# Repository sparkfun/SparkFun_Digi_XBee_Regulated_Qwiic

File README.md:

SparkFun Digi XBee® Explorer Regulated
========================================

[*SparkFun Digi XBee® Explorer Regulated (22032)*](https://www.sparkfun.com/products/22032)

Unleash the power of Digi XBee® modules with the next-gen SparkFun Digi XBee® Explorer Regulated! This versatile breakout board bypasses a USB-C connection, packing all the XBee functionality you need alongside the power of Digi's newest XBee 3 modules (XBee 3 LTE-M/NB-IoT and XBee RR Pro) into a single, convenient solution. The SparkFun Digi XBee® Explorer Regulated is the perfect companion for any low-power cellular IoT project. Its simplicity, versatility, and robust features make it ideal for beginners and seasoned developers.

The SparkFun Digi XBee® Explorer Regulated streamlines your workflow, providing everything you need to get started. Power is provided through the PTH headers, and the board retains its power regulation capabilities. You can enable the Qwiic connector for all those lovely I<sup>2</sup>C sensors and Reset and D0 buttons.

Repository Contents
-------------------

* **/Hardware** - Eagle design files (.brd, .sch)
* **/Production** - Production panel files (.brd)
* **/docs** - Related software for the Sparkfun Digi XBee® Arduino Shield

Documentation
--------------
* **[Hookup Guide](http://docs.sparkfun.com/SparkFun_Digi_XBee_Regulated_Qwiic)** - Basic hookup guide for the SparkFun Digi XBee® Explorer Regulated.

License Information
-------------------

This product is _**open source**_! 

Please review the LICENSE.md file for license information. 

If you have any questions or concerns on licensing, please contact technical support on our [SparkFun forums](https://forum.sparkfun.com/viewforum.php?f=152).

Distributed as-is; no warranty is given.

- Your friends at SparkFun.

_<COLLABORATION CREDIT>_

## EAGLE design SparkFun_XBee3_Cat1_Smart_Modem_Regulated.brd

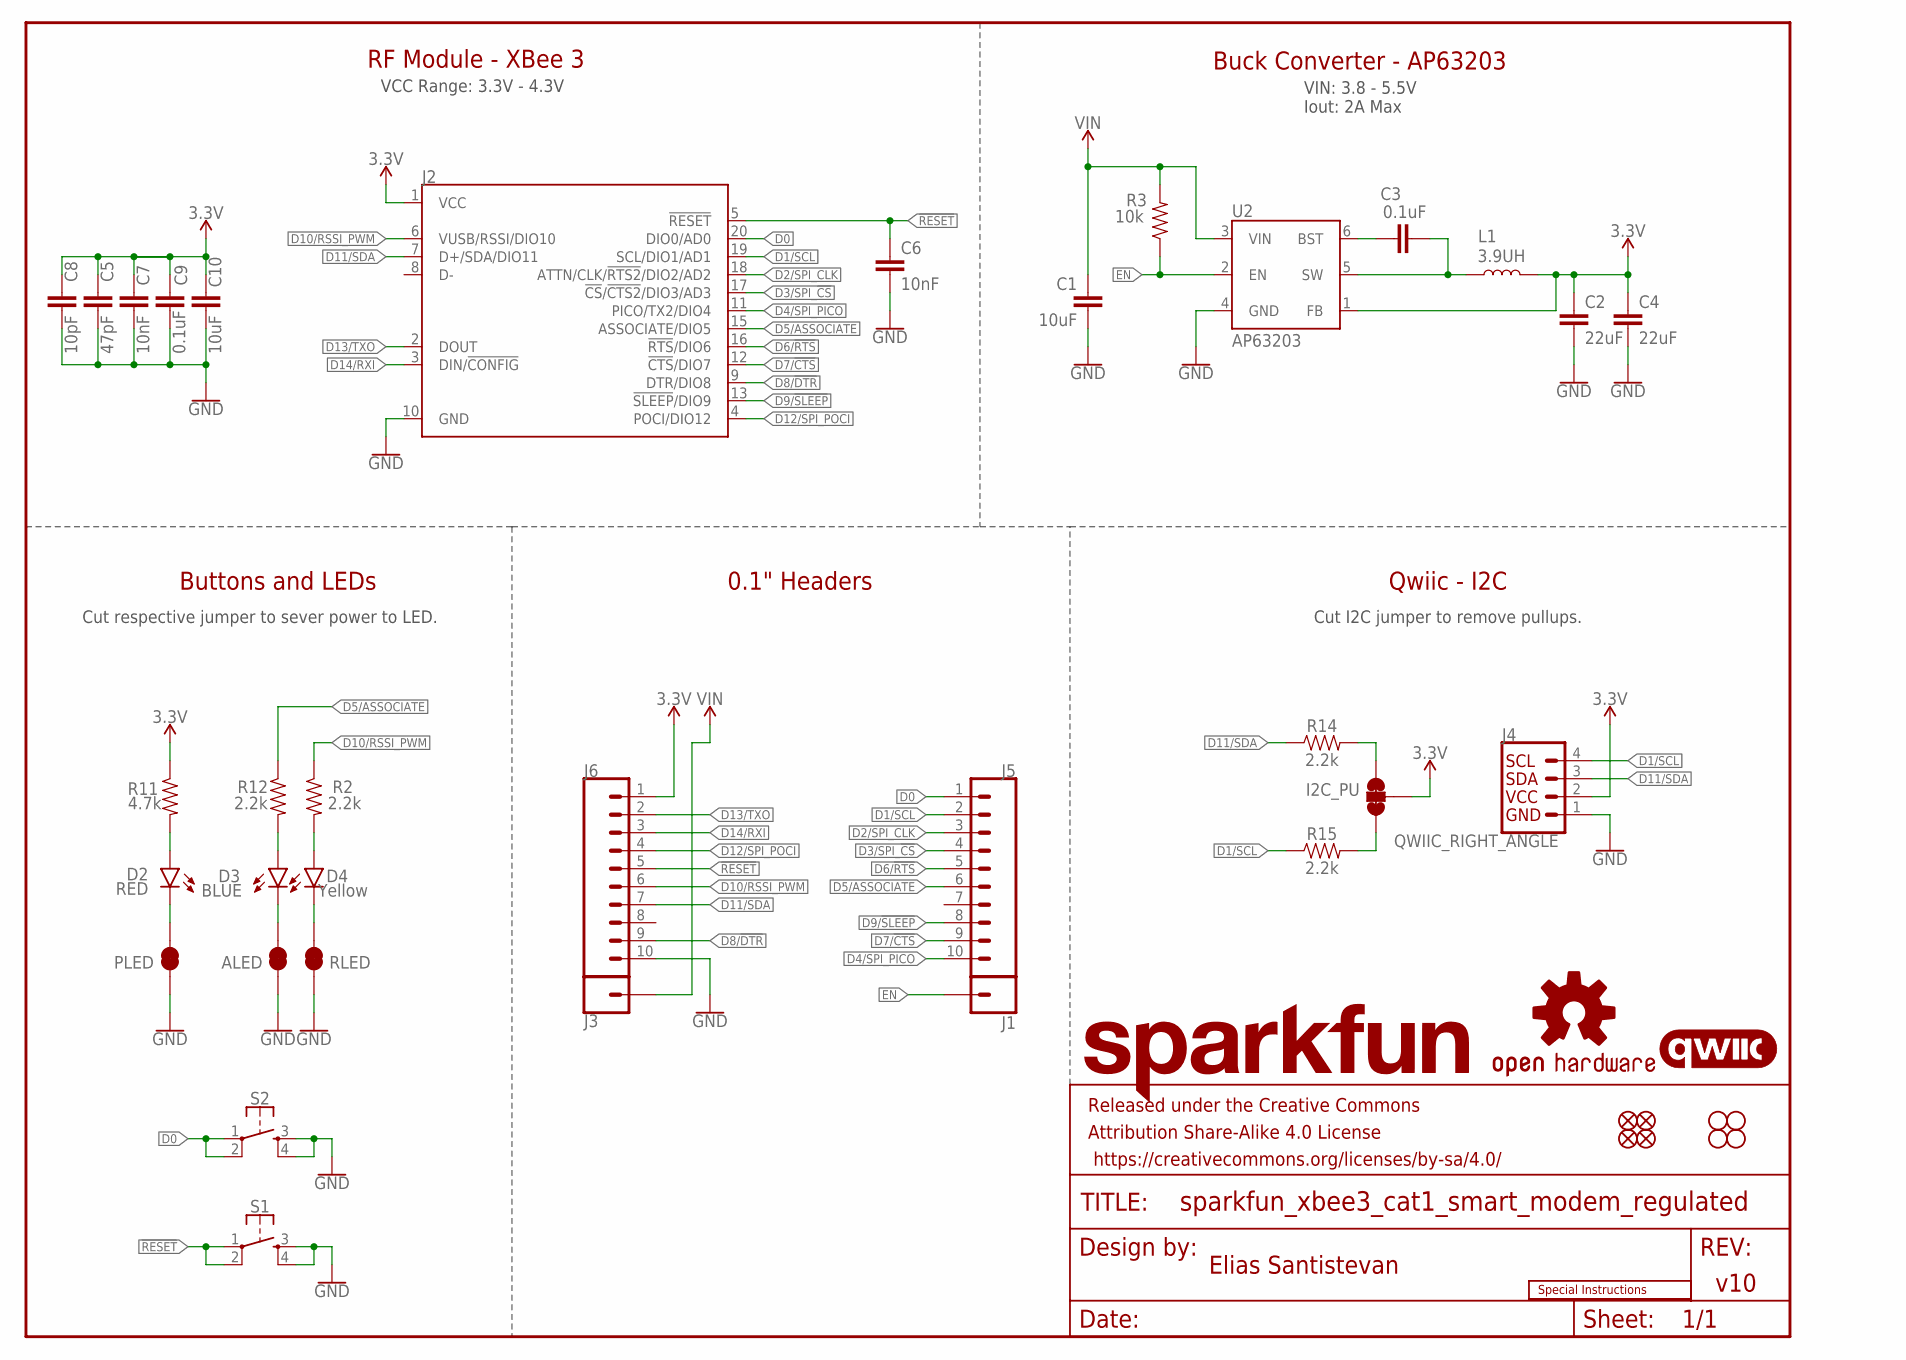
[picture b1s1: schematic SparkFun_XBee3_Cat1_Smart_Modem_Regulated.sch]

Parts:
ALED: JUMPER-SMT_2_NC_TRACE_SILK; SMT-JUMPER_2_NC_TRACE_SILK
C1: 10uF; 1210
C2, C4: 22uF; 0603
C3, C9: 0.1uF; 0603
C5: 47pF; 0603
C6, C7: 10nF; 0603
C8: 10pF; 0603
C10: 10uF; 0603
D2: RED; LED-0603
D3: BLUE; LED-0603
D4: Yellow; LED-0603
FD1, FD2, FD3, FD4: FIDUCIAL1X2; FIDUCIAL-1X2
FRAME2: FRAME-LETTER; CREATIVE_COMMONS
H1, H2, H3, H4: STAND-OFFTIGHT; STAND-OFF-TIGHT
I2C_PU: JUMPER-SMT_3_2-NC_TRACE_SILK; SMT-JUMPER_3_2-NC_TRACE_SILK
J1, J3: CONN_01PTH_NO_SILK_STAND; 1X01_NO_SILK_STAND
J2: XBEE_UPDATEXBEE_SMD; XBEE3-SMD
J4: QWIIC_RIGHT_ANGLE; JST04_1MM_RA
J5, J6: CONN_10NO_SILK_PTH_FEMALE; 1X10_NO_SILK
L1: 3.9UH; INDUCTOR_3.9UH
LOGO1: SPECIAL_INSTRUCTIONS-ORDERING; ORDERING_INSTRUCTIONS
LOGO2: OSHW-LOGOS; OSHW-LOGO-S
LOGO3: QWIIC_LOGO_4MM; QWIIC_4MM
LOGO4: SFE_LOGO_NAMEBLANK; BLANK
PLED: JUMPER-SMT_2_NC_TRACE_SILK; SMT-JUMPER_2_NC_TRACE_SILK
R2, R12, R14, R15: 2.2k; 0603
R3: 10k; 0603
R11: 4.7k; 0603
RLED: JUMPER-SMT_2_NC_TRACE_SILK; SMT-JUMPER_2_NC_TRACE_SILK
S1, S2: MOMENTARY-SWITCH-SPST-2-SMD-5.2MM-TALL; TACTILE_SWITCH_SMD_5.2MM
U2: AP63203; SOT23-6

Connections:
3.3V: C2.1, C4.1, C5.1, C7.1, C8.1, C9.1, C10.1, I2C_PU.2, J2.1 (VCC), J4.2, J6.1, L1.P$2 (2), R11.1, U2.1 (FB)
!RESET!: C6.1, J2.5 (!RESET!), J6.5, S1.1, S1.2
D0: J2.20 (DIO0/AD0), J5.1, S2.1, S2.2
D1/SCL: J2.19 (SCL/DIO1/AD1), J4.4, J5.2, R15.1
D2/SPI_CLK: J2.18 (ATTN/CLK/!RTS2!/DIO2/AD2), J5.3
D3/SPI_!CS!: J2.17 (!CS!/!CTS2!/DIO3/AD3), J5.4
D4/SPI_PICO: J2.11 (PICO/TX2/DIO4), J5.10
D5/ASSOCIATE: J2.15 (ASSOCIATE/DIO5), J5.6, R12.1
D6/!RTS!: J2.16 (!RTS!/DIO6), J5.5
D7/!CTS!: J2.12 (!CTS!/DIO7), J5.9
D8/!DTR!: J2.9 (DTR/DIO8), J6.9
D9/!SLEEP!: J2.13 (!SLEEP!/DIO9), J5.8
D10/RSSI_PWM: J2.6 (VUSB/RSSI/DIO10), J6.6, R2.1
D11/SDA: J2.7 (D+/SDA/DIO11), J4.3, J6.7, R14.1
D12/SPI_POCI: J2.4 (POCI/DIO12), J6.4
D13/TXO: J2.2 (DOUT), J6.2
D14/RXI: J2.3 (DIN/!CONFIG!), J6.3
EN: J1.1, R3.1, U2.2 (EN)
GND: ALED.1, C1.2, C2.2, C4.2, C5.2, C6.2, C7.2, C8.2, C9.2, C10.2, J2.10 (GND), J4.1, J6.10, PLED.1, RLED.1, S1.3, S1.4, S2.3, S2.4, U2.4 (GND)
unnamed: C3.1, U2.6 (BST)
unnamed: D4.A, R2.2
unnamed: D4.C, RLED.2
unnamed: D2.A, R11.2
unnamed: C3.2, L1.P$1 (1), U2.5 (SW)
unnamed: I2C_PU.3, R14.2
unnamed: D3.A, R12.2
unnamed: I2C_PU.1, R15.2
unnamed: ALED.2, D3.C
unnamed: D2.C, PLED.2
VIN: C1.1, J3.1, R3.2, U2.3 (VIN)

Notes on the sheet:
VCC Range: 3.3V - 4.3V
Buck Converter - AP63203
Qwiic - I2C
v10
Elias Santistevan
Buttons and LEDs
VIN: 3.8 - 5.5V Iout: 2A Max
Cut I2C jumper to remove pullups.
Cut respective jumper to sever power to LED.
RF Module - XBee 3
0.1" Headers

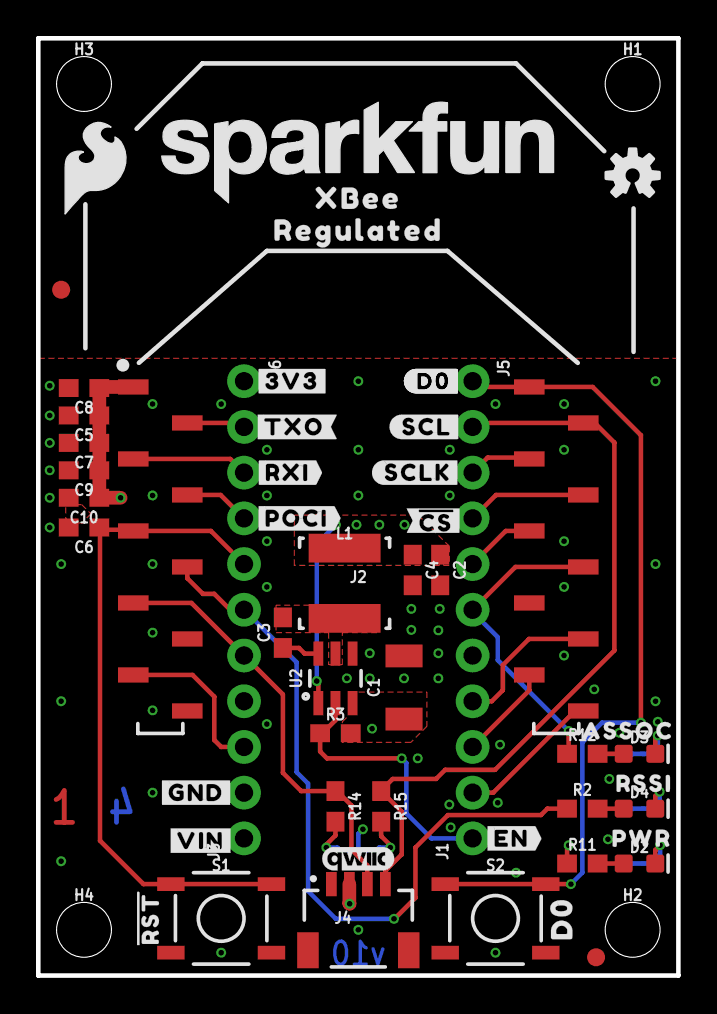
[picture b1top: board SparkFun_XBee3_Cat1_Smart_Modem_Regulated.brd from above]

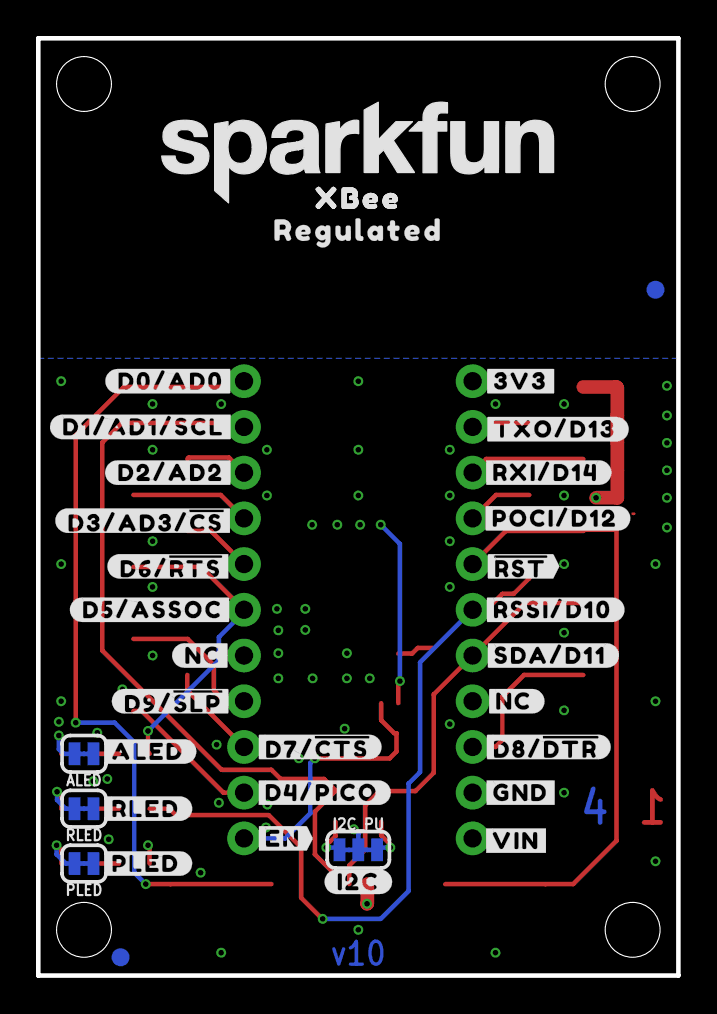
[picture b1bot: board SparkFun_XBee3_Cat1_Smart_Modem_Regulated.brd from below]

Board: 4 copper layers, 35.6 x 52.1 mm, 97 parts (36 on the bottom side), 30 nets.

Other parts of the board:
U$1, U$12: #GND#0
U$2, U$63: SFE_LOGO_NAME_.2
U$3, U$6: #EN#17
U$4: #NC#1
U$5: #NC#3
U$7: #D7##CTS##26
U$8: #D0#AD0#18
U$9, U$44: #3V3#1
U$10: #D4#PICO#25
U$11: #RLED#22
U$13: #D8##DTR##27
U$14: #RSSI#D10#17
U$15: #SDA#D11#9
U$16: ##RST##15
U$17: #POCI#D12#24
U$18: #RXI#D14#15
U$19: #D2#AD2#19
U$20: #D6##RTS##25
U$21: #TXO#8
U$22: #TXO#D13#13
U$23, U$25, U$28: XBEE340
U$24, U$29: REGULATED1343
U$26: #I2C#33
U$27: #RXI#7
U$30: #RST#30
U$31, U$65: #D0#3
U$32: #D1#AD1#SCL#8
U$34: #D3#AD3##CS##23
U$35: #D5#ASSOC#25
U$36: #D9##SLP##28
U$40: D03
U$42: PWR26
U$43: ASSOC27
U$45: #POCI#32
U$46, U$66: #VIN#4
U$49: #ALED#21
U$52: #PLED#20
U$59: ##CS##26
U$60: #SCLK#33
U$61: SFE_LOGO_FLAME_.2
U$62: RSSI31
U$64: #SCL#9

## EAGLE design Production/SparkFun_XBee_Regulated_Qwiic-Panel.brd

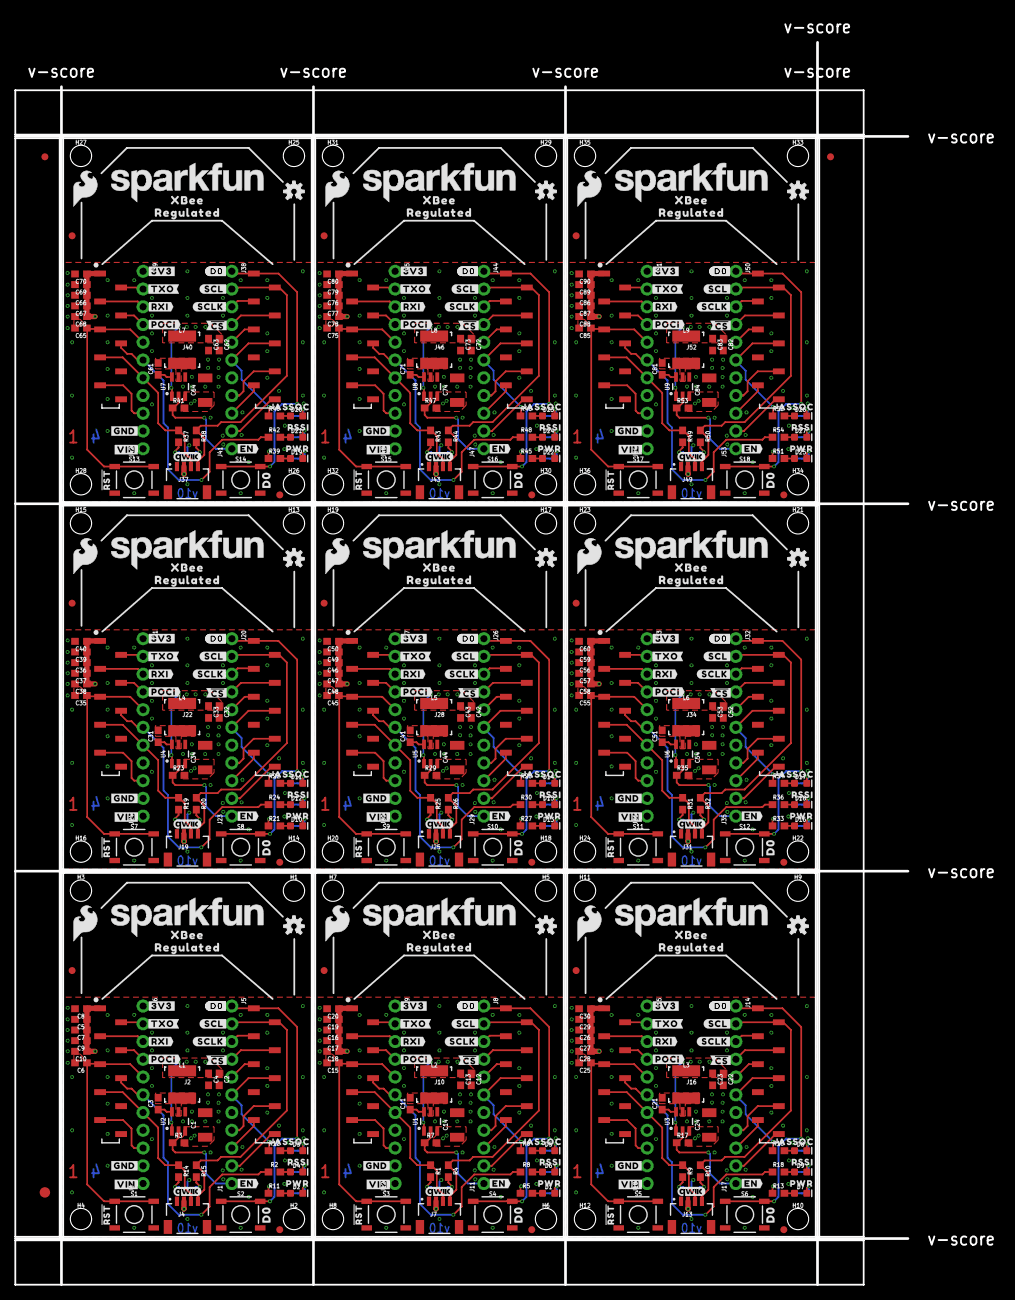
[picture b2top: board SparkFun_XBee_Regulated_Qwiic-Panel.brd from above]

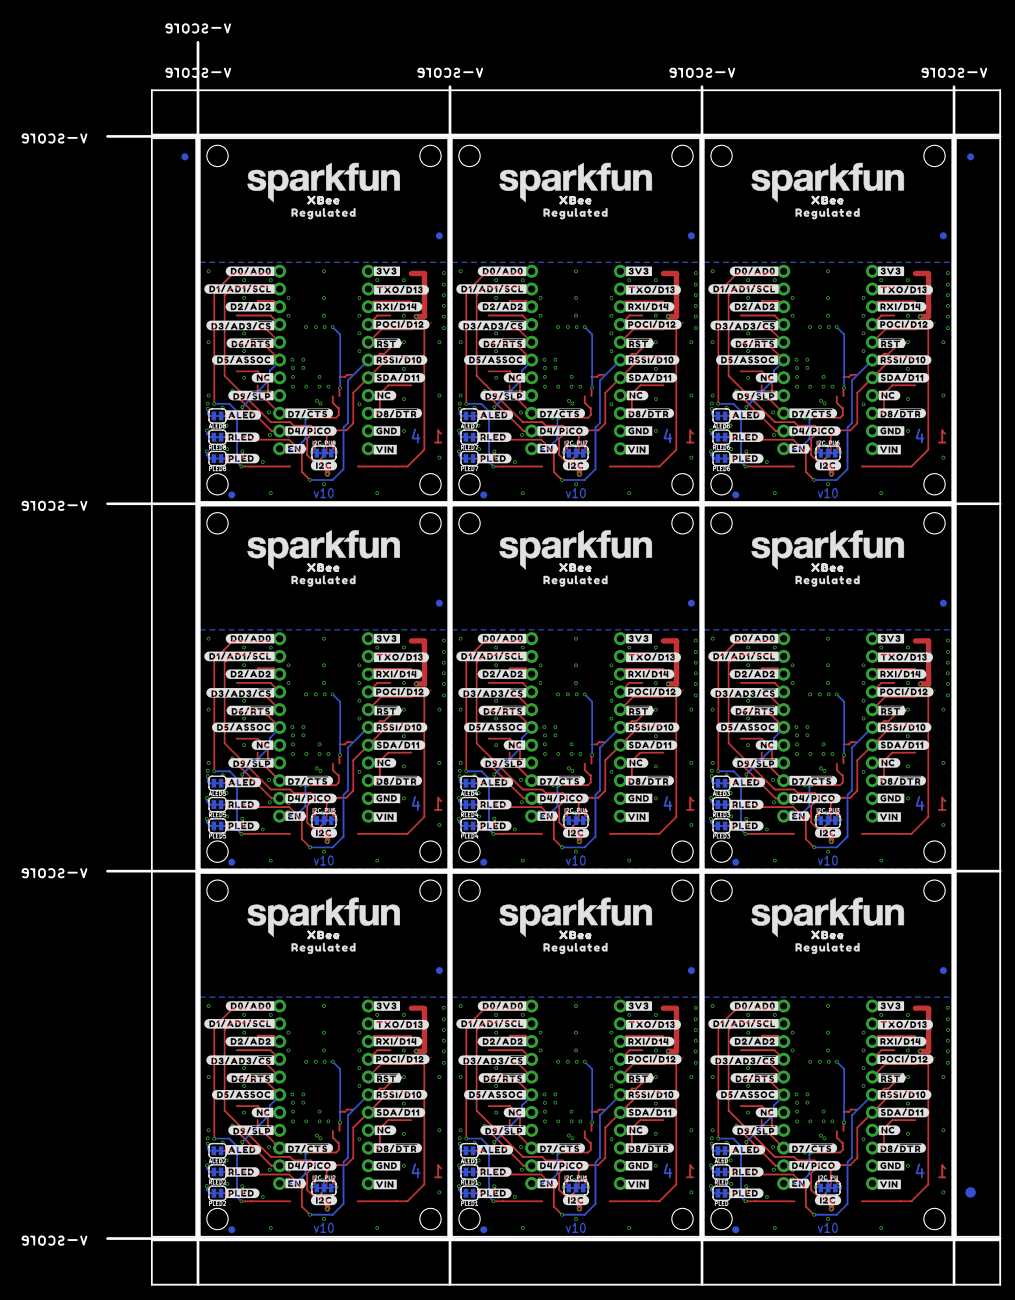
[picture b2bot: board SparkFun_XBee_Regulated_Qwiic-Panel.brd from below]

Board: 4 copper layers, 127.8 x 177.8 mm, 870 parts (327 on the bottom side), 270 nets.

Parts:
ALED, ALED1, ALED2, ALED3, ALED4, ALED5, ALED6, ALED7, ALED8: JUMPER-SMT_2_NC_TRACE_SILK; SMT-JUMPER_2_NC_TRACE_SILK
C1, C14, C24, C34, C44, C54, C64, C74, C84: 10uF; 1210
C2, C4, C12, C13, C22, C23, C32, C33, C42, C43, C52, C53, C62, C63, C72, C73, C82, C83: 22uF; 0603
C3, C9, C11, C17, C21, C27, C31, C37, C41, C47, C51, C57, C61, C67, C71, C77, C81, C87: 0.1uF; 0603
C5, C19, C29, C39, C49, C59, C69, C79, C89: 47pF; 0603
C6, C7, C15, C16, C25, C26, C35, C36, C45, C46, C55, C56, C65, C66, C75, C76, C85, C86: 10nF; 0603
C8, C20, C30, C40, C50, C60, C70, C80, C90: 10pF; 0603
C10, C18, C28, C38, C48, C58, C68, C78, C88: 10uF; 0603
D1, D2, D7, D10, D13, D16, D19, D22, D25: RED; LED-0603
D3, D5, D8, D11, D14, D17, D20, D23, D26: BLUE; LED-0603
D4, D6, D9, D12, D15, D18, D21, D24, D27: Yellow; LED-0603
E$1, E$2, E$3, E$4: FIDUCIAL-1X2
E$5, E$6: FIDUCIAL-1.5X3
FD1, FD2, FD3, FD4, FD5, FD6, FD7, FD8, FD9, FD10, FD11, FD12, FD13, FD14, FD15, FD16, FD17, FD18, FD19, FD20, FD21, FD22, FD23, FD24, FD25, FD26, FD27, FD28, FD29, FD30, FD31, FD32, FD33, FD34, FD35, FD36: FIDUCIAL1X2; FIDUCIAL-1X2
FRAME1, FRAME2, FRAME3, FRAME4, FRAME5, FRAME6, FRAME7, FRAME8, FRAME9: FRAME-LETTER; CREATIVE_COMMONS
H1, H2, H3, H4, H5, H6, H7, H8, H9, H10, H11, H12, H13, H14, H15, H16, H17, H18, H19, H20, H21, H22, H23, H24, H25, H26, H27, H28, H29, H30, H31, H32, H33, H34, H35, H36: STAND-OFFTIGHT; STAND-OFF-TIGHT
I2C_PU, I2C_PU1, I2C_PU2, I2C_PU3, I2C_PU4, I2C_PU5, I2C_PU6, I2C_PU7, I2C_PU8: JUMPER-SMT_3_2-NC_TRACE_SILK; SMT-JUMPER_3_2-NC_TRACE_SILK
J1, J3, J11, J12, J17, J18, J23, J24, J29, J30, J35, J36, J41, J42, J47, J48, J53, J54: 1X01_NO_SILK_STAND
J2, J10, J16, J22, J28, J34, J40, J46, J52: XBEE3-SMD
J4, J7, J13, J19, J25, J31, J37, J43, J49: QWIIC_RIGHT_ANGLE; JST04_1MM_RA
J5, J6, J8, J9, J14, J15, J20, J21, J26, J27, J32, J33, J38, J39, J44, J45, J50, J51: 1X10_NO_SILK
L1, L2, L3, L4, L5, L6, L7, L8, L9: 3.9UH; INDUCTOR_3.9UH
LOGO1, LOGO2, LOGO7, LOGO10, LOGO13, LOGO16, LOGO19, LOGO22, LOGO25: OSHW-LOGOS; OSHW-LOGO-S
LOGO3, LOGO5, LOGO8, LOGO11, LOGO14, LOGO17, LOGO20, LOGO23, LOGO26: QWIIC_LOGO_4MM; QWIIC_4MM
LOGO4, LOGO6, LOGO9, LOGO12, LOGO15, LOGO18, LOGO21, LOGO24, LOGO27: SFE_LOGO_NAMEBLANK; BLANK
PLED, PLED1, PLED2, PLED3, PLED4, PLED5, PLED6, PLED7, PLED8: JUMPER-SMT_2_NC_TRACE_SILK; SMT-JUMPER_2_NC_TRACE_SILK
R1, R2, R4, R6, R8, R9, R10, R12, R14, R15, R16, R18, R19, R20, R22, R24, R25, R26, R28, R30, R31, R32, R34, R36, R37, R38, R40, R42, R43, R44, R46, R48, R49, R50, R52, R54: 2.2k; 0603
R3, R7, R17, R23, R29, R35, R41, R47, R53: 10k; 0603
R5, R11, R13, R21, R27, R33, R39, R45, R51: 4.7k; 0603
RLED, RLED1, RLED2, RLED3, RLED4, RLED5, RLED6, RLED7, RLED8: JUMPER-SMT_2_NC_TRACE_SILK; SMT-JUMPER_2_NC_TRACE_SILK
S1, S2, S3, S4, S5, S6, S7, S8, S9, S10, S11, S12, S13, S14, S15, S16, S17, S18: TACTILE_SWITCH_SMD_5.2MM
U1, U2, U3, U4, U5, U6, U7, U8, U9: AP63203; SOT23-6
U$1, U$12, U$68, U$86, U$119, U$137, U$170, U$188, U$221, U$239, U$272, U$290, U$323, U$341, U$374, U$392, U$425, U$443: #GND#0
U$2, U$51, U$63, U$87, U$111, U$138, U$162, U$189, U$213, U$240, U$264, U$291, U$315, U$342, U$366, U$393, U$417, U$444: SFE_LOGO_NAME_.2
U$3, U$6, U$88, U$102, U$139, U$153, U$190, U$204, U$241, U$255, U$292, U$306, U$343, U$357, U$394, U$408, U$445, U$459: #EN#17
U$4, U$89, U$140, U$191, U$242, U$293, U$344, U$395, U$446: #NC#1
U$5, U$90, U$141, U$192, U$243, U$294, U$345, U$396, U$447: #NC#3
U$7, U$91, U$142, U$193, U$244, U$295, U$346, U$397, U$448: #D7##CTS##26
U$8, U$55, U$114, U$165, U$216, U$267, U$318, U$369, U$420: #D0#AD0#18
U$9, U$33, U$41, U$44, U$103, U$107, U$154, U$158, U$205, U$209, U$256, U$260, U$307, U$311, U$358, U$362, U$409, U$413: #3V3#1
U$10, U$92, U$143, U$194, U$245, U$296, U$347, U$398, U$449: #D4#PICO#25
U$11, U$100, U$151, U$202, U$253, U$304, U$355, U$406, U$457: #RLED#22
U$13, U$69, U$120, U$171, U$222, U$273, U$324, U$375, U$426: #D8##DTR##27
U$14, U$70, U$121, U$172, U$223, U$274, U$325, U$376, U$427: #RSSI#D10#17
U$15, U$71, U$122, U$173, U$224, U$275, U$326, U$377, U$428: #SDA#D11#9
U$16, U$72, U$123, U$174, U$225, U$276, U$327, U$378, U$429: ##RST##15
U$17, U$73, U$124, U$175, U$226, U$277, U$328, U$379, U$430: #POCI#D12#24
U$18, U$74, U$125, U$176, U$227, U$278, U$329, U$380, U$431: #RXI#D14#15
U$19, U$56, U$115, U$166, U$217, U$268, U$319, U$370, U$421: #D2#AD2#19
U$20, U$57, U$116, U$167, U$218, U$269, U$320, U$371, U$422: #D6##RTS##25
U$21, U$78, U$129, U$180, U$231, U$282, U$333, U$384, U$435: #TXO#8
U$22, U$75, U$126, U$177, U$228, U$279, U$330, U$381, U$432: #TXO#D13#13
U$23, U$25, U$28, U$94, U$95, U$96, U$145, U$146, U$147, U$196, U$197, U$198, U$247, U$248, U$249, U$298, U$299, U$300, U$349, U$350, U$351, U$400, U$401, U$402, U$451, U$452, U$453: XBEE340
U$24, U$29, U$93, U$97, U$144, U$148, U$195, U$199, U$246, U$250, U$297, U$301, U$348, U$352, U$399, U$403, U$450, U$454: REGULATED1343
U$26, U$37, U$104, U$155, U$206, U$257, U$308, U$359, U$410: #I2C#33
U$27, U$79, U$130, U$181, U$232, U$283, U$334, U$385, U$436: #RXI#7
U$30, U$50, U$110, U$161, U$212, U$263, U$314, U$365, U$416: #RST#30
U$31, U$65, U$84, U$98, U$135, U$149, U$186, U$200, U$237, U$251, U$288, U$302, U$339, U$353, U$390, U$404, U$441, U$455: #D0#3
U$32, U$99, U$150, U$201, U$252, U$303, U$354, U$405, U$456: #D1#AD1#SCL#8
U$34, U$101, U$152, U$203, U$254, U$305, U$356, U$407, U$458: #D3#AD3##CS##23
U$35, U$58, U$117, U$168, U$219, U$270, U$321, U$372, U$423: #D5#ASSOC#25
U$36, U$67, U$118, U$169, U$220, U$271, U$322, U$373, U$424: #D9##SLP##28
U$38, U$42, U$105, U$156, U$207, U$258, U$309, U$360, U$411: PWR26
U$39, U$43, U$106, U$157, U$208, U$259, U$310, U$361, U$412: ASSOC27
U$40, U$48, U$109, U$160, U$211, U$262, U$313, U$364, U$415: D03
U$45, U$80, U$131, U$182, U$233, U$284, U$335, U$386, U$437: #POCI#32
U$46, U$47, U$66, U$85, U$108, U$136, U$159, U$187, U$210, U$238, U$261, U$289, U$312, U$340, U$363, U$391, U$414, U$442: #VIN#4
U$49, U$76, U$127, U$178, U$229, U$280, U$331, U$382, U$433: #ALED#21
U$52, U$77, U$128, U$179, U$230, U$281, U$332, U$383, U$434: #PLED#20
U$53, U$61, U$112, U$163, U$214, U$265, U$316, U$367, U$418: SFE_LOGO_FLAME_.2
U$54, U$62, U$113, U$164, U$215, U$266, U$317, U$368, U$419: RSSI31
U$59, U$81, U$132, U$183, U$234, U$285, U$336, U$387, U$438: ##CS##26
U$60, U$82, U$133, U$184, U$235, U$286, U$337, U$388, U$439: #SCLK#33
U$64, U$83, U$134, U$185, U$236, U$287, U$338, U$389, U$440: #SCL#9

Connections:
3.3V: C2.1, C4.1, C5.1, C7.1, C8.1, C9.1, C10.1, I2C_PU.2, J2.1, J4.2, J6.1, L1.P$2, R11.1, U2.1
3.3V1: C12.1, C13.1, C16.1, C17.1, C18.1, C19.1, C20.1, I2C_PU1.2, J7.2, J9.1, J10.1, L2.P$2, R5.1, U1.1
3.3V2: C22.1, C23.1, C26.1, C27.1, C28.1, C29.1, C30.1, I2C_PU2.2, J13.2, J15.1, J16.1, L3.P$2, R13.1, U3.1
3.3V3: C32.1, C33.1, C36.1, C37.1, C38.1, C39.1, C40.1, I2C_PU3.2, J19.2, J21.1, J22.1, L4.P$2, R21.1, U4.1
3.3V4: C42.1, C43.1, C46.1, C47.1, C48.1, C49.1, C50.1, I2C_PU4.2, J25.2, J27.1, J28.1, L5.P$2, R27.1, U5.1
3.3V5: C52.1, C53.1, C56.1, C57.1, C58.1, C59.1, C60.1, I2C_PU5.2, J31.2, J33.1, J34.1, L6.P$2, R33.1, U6.1
3.3V6: C62.1, C63.1, C66.1, C67.1, C68.1, C69.1, C70.1, I2C_PU6.2, J37.2, J39.1, J40.1, L7.P$2, R39.1, U7.1
3.3V7: C72.1, C73.1, C76.1, C77.1, C78.1, C79.1, C80.1, I2C_PU7.2, J43.2, J45.1, J46.1, L8.P$2, R45.1, U8.1
3.3V8: C82.1, C83.1, C86.1, C87.1, C88.1, C89.1, C90.1, I2C_PU8.2, J49.2, J51.1, J52.1, L9.P$2, R51.1, U9.1
!RESET!: C6.1, J2.5, J6.5, S1.1, S1.2
!RESET!1: C15.1, J9.5, J10.5, S3.1, S3.2
!RESET!2: C25.1, J15.5, J16.5, S5.1, S5.2
!RESET!3: C35.1, J21.5, J22.5, S7.1, S7.2
!RESET!4: C45.1, J27.5, J28.5, S9.1, S9.2
!RESET!5: C55.1, J33.5, J34.5, S11.1, S11.2
!RESET!6: C65.1, J39.5, J40.5, S13.1, S13.2
!RESET!7: C75.1, J45.5, J46.5, S15.1, S15.2
!RESET!8: C85.1, J51.5, J52.5, S17.1, S17.2
D0: J2.20, J5.1, S2.1, S2.2
D1: J8.1, J10.20, S4.1, S4.2
D1/SCL: J2.19, J4.4, J5.2, R15.1
D1/SCL1: J7.4, J8.2, J10.19, R4.1
D1/SCL2: J13.4, J14.2, J16.19, R10.1
D1/SCL3: J19.4, J20.2, J22.19, R20.1
D1/SCL4: J25.4, J26.2, J28.19, R26.1
D1/SCL5: J31.4, J32.2, J34.19, R32.1
D1/SCL6: J37.4, J38.2, J40.19, R38.1
D1/SCL7: J43.4, J44.2, J46.19, R44.1
D1/SCL8: J49.4, J50.2, J52.19, R50.1
D2: J14.1, J16.20, S6.1, S6.2
D2/SPI_CLK: J2.18, J5.3
D2/SPI_CLK1: J8.3, J10.18
D2/SPI_CLK2: J14.3, J16.18
D2/SPI_CLK3: J20.3, J22.18
D2/SPI_CLK4: J26.3, J28.18
D2/SPI_CLK5: J32.3, J34.18
D2/SPI_CLK6: J38.3, J40.18
D2/SPI_CLK7: J44.3, J46.18
D2/SPI_CLK8: J50.3, J52.18
D3: J20.1, J22.20, S8.1, S8.2
D3/SPI_!CS!: J2.17, J5.4
D3/SPI_!CS!1: J8.4, J10.17
D3/SPI_!CS!2: J14.4, J16.17
D3/SPI_!CS!3: J20.4, J22.17
D3/SPI_!CS!4: J26.4, J28.17
D3/SPI_!CS!5: J32.4, J34.17
D3/SPI_!CS!6: J38.4, J40.17
D3/SPI_!CS!7: J44.4, J46.17
D3/SPI_!CS!8: J50.4, J52.17
D4: J26.1, J28.20, S10.1, S10.2
D4/SPI_PICO: J2.11, J5.10
D4/SPI_PICO1: J8.10, J10.11
D4/SPI_PICO2: J14.10, J16.11
D4/SPI_PICO3: J20.10, J22.11
D4/SPI_PICO4: J26.10, J28.11
D4/SPI_PICO5: J32.10, J34.11
D4/SPI_PICO6: J38.10, J40.11
D4/SPI_PICO7: J44.10, J46.11
D4/SPI_PICO8: J50.10, J52.11
D5: J32.1, J34.20, S12.1, S12.2
D5/ASSOCIATE: J2.15, J5.6, R12.1
D5/ASSOCIATE1: J8.6, J10.15, R6.1
D5/ASSOCIATE2: J14.6, J16.15, R16.1
D5/ASSOCIATE3: J20.6, J22.15, R22.1
D5/ASSOCIATE4: J26.6, J28.15, R28.1
D5/ASSOCIATE5: J32.6, J34.15, R34.1
D5/ASSOCIATE6: J38.6, J40.15, R40.1
D5/ASSOCIATE7: J44.6, J46.15, R46.1
D5/ASSOCIATE8: J50.6, J52.15, R52.1
D6: J38.1, J40.20, S14.1, S14.2
D6/!RTS!: J2.16, J5.5
D6/!RTS!1: J8.5, J10.16
D6/!RTS!2: J14.5, J16.16
D6/!RTS!3: J20.5, J22.16
D6/!RTS!4: J26.5, J28.16
D6/!RTS!5: J32.5, J34.16
D6/!RTS!6: J38.5, J40.16
D6/!RTS!7: J44.5, J46.16
D6/!RTS!8: J50.5, J52.16
D7: J44.1, J46.20, S16.1, S16.2
D7/!CTS!: J2.12, J5.9
D7/!CTS!1: J8.9, J10.12
D7/!CTS!2: J14.9, J16.12
D7/!CTS!3: J20.9, J22.12
D7/!CTS!4: J26.9, J28.12
D7/!CTS!5: J32.9, J34.12
D7/!CTS!6: J38.9, J40.12
D7/!CTS!7: J44.9, J46.12
D7/!CTS!8: J50.9, J52.12
D8: J50.1, J52.20, S18.1, S18.2
D8/!DTR!: J2.9, J6.9
D8/!DTR!1: J9.9, J10.9
D8/!DTR!2: J15.9, J16.9
D8/!DTR!3: J21.9, J22.9
D8/!DTR!4: J27.9, J28.9
D8/!DTR!5: J33.9, J34.9
D8/!DTR!6: J39.9, J40.9
D8/!DTR!7: J45.9, J46.9
D8/!DTR!8: J51.9, J52.9
D9/!SLEEP!: J2.13, J5.8
D9/!SLEEP!1: J8.8, J10.13
D9/!SLEEP!2: J14.8, J16.13
D9/!SLEEP!3: J20.8, J22.13
D9/!SLEEP!4: J26.8, J28.13
D9/!SLEEP!5: J32.8, J34.13
D9/!SLEEP!6: J38.8, J40.13
D9/!SLEEP!7: J44.8, J46.13
D9/!SLEEP!8: J50.8, J52.13
D10/RSSI_PWM: J2.6, J6.6, R2.1
D10/RSSI_PWM1: J9.6, J10.6, R8.1
D10/RSSI_PWM2: J15.6, J16.6, R18.1
D10/RSSI_PWM3: J21.6, J22.6, R24.1
D10/RSSI_PWM4: J27.6, J28.6, R30.1
D10/RSSI_PWM5: J33.6, J34.6, R36.1
D10/RSSI_PWM6: J39.6, J40.6, R42.1
D10/RSSI_PWM7: J45.6, J46.6, R48.1
D10/RSSI_PWM8: J51.6, J52.6, R54.1
D11/SDA: J2.7, J4.3, J6.7, R14.1
D11/SDA1: J7.3, J9.7, J10.7, R1.1
D11/SDA2: J13.3, J15.7, J16.7, R9.1
D11/SDA3: J19.3, J21.7, J22.7, R19.1
D11/SDA4: J25.3, J27.7, J28.7, R25.1
D11/SDA5: J31.3, J33.7, J34.7, R31.1
D11/SDA6: J37.3, J39.7, J40.7, R37.1
D11/SDA7: J43.3, J45.7, J46.7, R43.1
D11/SDA8: J49.3, J51.7, J52.7, R49.1
D12/SPI_POCI: J2.4, J6.4
D12/SPI_POCI1: J9.4, J10.4
D12/SPI_POCI2: J15.4, J16.4
D12/SPI_POCI3: J21.4, J22.4
D12/SPI_POCI4: J27.4, J28.4
D12/SPI_POCI5: J33.4, J34.4
D12/SPI_POCI6: J39.4, J40.4
D12/SPI_POCI7: J45.4, J46.4
D12/SPI_POCI8: J51.4, J52.4
D13/TXO: J2.2, J6.2
D13/TXO1: J9.2, J10.2
D13/TXO2: J15.2, J16.2
D13/TXO3: J21.2, J22.2
D13/TXO4: J27.2, J28.2
D13/TXO5: J33.2, J34.2
D13/TXO6: J39.2, J40.2
D13/TXO7: J45.2, J46.2
D13/TXO8: J51.2, J52.2
D14/RXI: J2.3, J6.3
D14/RXI1: J9.3, J10.3
D14/RXI2: J15.3, J16.3
D14/RXI3: J21.3, J22.3
D14/RXI4: J27.3, J28.3
D14/RXI5: J33.3, J34.3
D14/RXI6: J39.3, J40.3
D14/RXI7: J45.3, J46.3
D14/RXI8: J51.3, J52.3
EN: J1.1, R3.1, U2.2
EN1: J11.1, R7.1, U1.2
EN2: J17.1, R17.1, U3.2
EN3: J23.1, R23.1, U4.2
EN4: J29.1, R29.1, U5.2
EN5: J35.1, R35.1, U6.2
EN6: J41.1, R41.1, U7.2
EN7: J47.1, R47.1, U8.2
EN8: J53.1, R53.1, U9.2
GND: ALED.1, C1.2, C2.2, C4.2, C5.2, C6.2, C7.2, C8.2, C9.2, C10.2, J2.10, J4.1, J6.10, PLED.1, RLED.1, S1.3, S1.4, S2.3, S2.4, U2.4
GND1: ALED1.1, C12.2, C13.2, C14.2, C15.2, C16.2, C17.2, C18.2, C19.2, C20.2, J7.1, J9.10, J10.10, PLED1.1, RLED1.1, S3.3, S3.4, S4.3, S4.4, U1.4
GND2: ALED2.1, C22.2, C23.2, C24.2, C25.2, C26.2, C27.2, C28.2, C29.2, C30.2, J13.1, J15.10, J16.10, PLED2.1, RLED2.1, S5.3, S5.4, S6.3, S6.4, U3.4
GND3: ALED3.1, C32.2, C33.2, C34.2, C35.2, C36.2, C37.2, C38.2, C39.2, C40.2, J19.1, J21.10, J22.10, PLED3.1, RLED3.1, S7.3, S7.4, S8.3, S8.4, U4.4
GND4: ALED4.1, C42.2, C43.2, C44.2, C45.2, C46.2, C47.2, C48.2, C49.2, C50.2, J25.1, J27.10, J28.10, PLED4.1, RLED4.1, S9.3, S9.4, S10.3, S10.4, U5.4
GND5: ALED5.1, C52.2, C53.2, C54.2, C55.2, C56.2, C57.2, C58.2, C59.2, C60.2, J31.1, J33.10, J34.10, PLED5.1, RLED5.1, S11.3, S11.4, S12.3, S12.4, U6.4
GND6: ALED6.1, C62.2, C63.2, C64.2, C65.2, C66.2, C67.2, C68.2, C69.2, C70.2, J37.1, J39.10, J40.10, PLED6.1, RLED6.1, S13.3, S13.4, S14.3, S14.4, U7.4
GND7: ALED7.1, C72.2, C73.2, C74.2, C75.2, C76.2, C77.2, C78.2, C79.2, C80.2, J43.1, J45.10, J46.10, PLED7.1, RLED7.1, S15.3, S15.4, S16.3, S16.4, U8.4
GND8: ALED8.1, C82.2, C83.2, C84.2, C85.2, C86.2, C87.2, C88.2, C89.2, C90.2, J49.1, J51.10, J52.10, PLED8.1, RLED8.1, S17.3, S17.4, S18.3, S18.4, U9.4
unnamed: C3.1, U2.6
unnamed: D4.A, R2.2
unnamed: D4.C, RLED.2
unnamed: I2C_PU1.3, R1.2
unnamed: I2C_PU1.1, R4.2
unnamed: D1.A, R5.2
unnamed: D2.A, R11.2
unnamed: C3.2, L1.P$1, U2.5
unnamed: D5.A, R6.2
unnamed: ALED1.2, D5.C
unnamed: I2C_PU.3, R14.2
unnamed: D3.A, R12.2
unnamed: I2C_PU.1, R15.2
unnamed: D1.C, PLED1.2
unnamed: C11.1, U1.6
unnamed: C11.2, L2.P$1, U1.5
unnamed: D6.A, R8.2
unnamed: D6.C, RLED1.2
unnamed: I2C_PU2.3, R9.2
unnamed: I2C_PU2.1, R10.2
unnamed: ALED.2, D3.C
unnamed: D7.A, R13.2
unnamed: D2.C, PLED.2
unnamed: D8.A, R16.2
unnamed: ALED2.2, D8.C
unnamed: D7.C, PLED2.2
unnamed: C21.1, U3.6
unnamed: C21.2, L3.P$1, U3.5
unnamed: D9.A, R18.2
unnamed: D9.C, RLED2.2
unnamed: I2C_PU3.3, R19.2
unnamed: I2C_PU3.1, R20.2
unnamed: D10.A, R21.2
unnamed: D11.A, R22.2
unnamed: ALED3.2, D11.C
unnamed: D10.C, PLED3.2
unnamed: C31.1, U4.6
unnamed: C31.2, L4.P$1, U4.5
unnamed: D12.A, R24.2
unnamed: D12.C, RLED3.2
unnamed: I2C_PU4.3, R25.2
unnamed: I2C_PU4.1, R26.2
unnamed: D13.A, R27.2
unnamed: D14.A, R28.2
unnamed: ALED4.2, D14.C
unnamed: D13.C, PLED4.2
unnamed: C41.1, U5.6
unnamed: C41.2, L5.P$1, U5.5
unnamed: D15.A, R30.2
unnamed: D15.C, RLED4.2
unnamed: I2C_PU5.3, R31.2
unnamed: I2C_PU5.1, R32.2
unnamed: D16.A, R33.2
unnamed: D17.A, R34.2
unnamed: ALED5.2, D17.C
unnamed: D16.C, PLED5.2
unnamed: C51.1, U6.6
unnamed: C51.2, L6.P$1, U6.5
unnamed: D18.A, R36.2
unnamed: D18.C, RLED5.2
unnamed: I2C_PU6.3, R37.2
unnamed: I2C_PU6.1, R38.2
unnamed: D19.A, R39.2
unnamed: D20.A, R40.2
unnamed: ALED6.2, D20.C
unnamed: D19.C, PLED6.2
unnamed: C61.1, U7.6
unnamed: C61.2, L7.P$1, U7.5
unnamed: D21.A, R42.2
unnamed: D21.C, RLED6.2
unnamed: I2C_PU7.3, R43.2
unnamed: I2C_PU7.1, R44.2
unnamed: D22.A, R45.2
unnamed: D23.A, R46.2
unnamed: ALED7.2, D23.C
unnamed: D22.C, PLED7.2
unnamed: C71.1, U8.6
unnamed: C71.2, L8.P$1, U8.5
unnamed: D24.A, R48.2
unnamed: D24.C, RLED7.2
unnamed: I2C_PU8.3, R49.2
unnamed: I2C_PU8.1, R50.2
unnamed: D25.A, R51.2
unnamed: D26.A, R52.2
unnamed: ALED8.2, D26.C
unnamed: D25.C, PLED8.2
unnamed: C81.1, U9.6
unnamed: C81.2, L9.P$1, U9.5
unnamed: D27.A, R54.2
unnamed: D27.C, RLED8.2
VIN: C1.1, J3.1, R3.2, U2.3
VIN1: C14.1, J12.1, R7.2, U1.3
VIN2: C24.1, J18.1, R17.2, U3.3
VIN3: C34.1, J24.1, R23.2, U4.3
VIN4: C44.1, J30.1, R29.2, U5.3
VIN5: C54.1, J36.1, R35.2, U6.3
VIN6: C64.1, J42.1, R41.2, U7.3
VIN7: C74.1, J48.1, R47.2, U8.3
VIN8: C84.1, J54.1, R53.2, U9.3

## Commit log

2023-01-31 Routes the board (roughly)
2023-01-31 Adds silk
2023-01-31 MOves to a smaller schematic symbol, tries to make the associate LED visible
2023-01-31 MOre vias
2023-03-01 Adds two additional layers, routes all nets, adds most silk
2023-03-01 Adds more silk labels, Adds ordering instructions
2023-03-01 Moves some silk around
2023-03-01 Adds four layer numbers, fixes accidental naming of GND to "OPEN"
2023-03-01 Moves LEDs around for consistency with the development board
2023-03-01 Approves DRC errors caused by jumpers
2023-03-02 Adds vias, fixes acid traps, moves LEDs away from the edge
2023-03-02 Moves I2C jumper down to make more space for the silk in that area
2023-03-02 Adds vias!!
2023-03-03 Renames board files
2023-03-03 Adds production panels
2023-03-08 Adds "Explorer" to silk
2023-03-08 Updates silk on production files
2023-08-02 Checking in override files
2023-08-02 Initial pass of docs pages
2023-09-18 Updating page descriptions
2023-11-27 Updating with latest
2023-11-29 Updating layout and adding action shot
2023-12-12 Adding setuptools to build and cleaning up names
2023-12-22 Update to overview
2024-01-02 Adding buck converter image
2024-01-03 Updates to links and hardware overview
2024-01-05 Updates to Product trademarks per Digi
2024-01-05 Deployed 258aacc with MkDocs version: 1.5.3
2024-05-17 Deployed fc05a67 with MkDocs version: 1.6.0
2026-06-03 Deployed 0e25ebd with MkDocs version: 1.6.1

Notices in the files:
parts and their libraries:
SparkFun-Capacitors: Licensing: Creative Commons ShareAlike 4.0 International - https://creativecommons.org/licenses/by-sa/4.0
SparkFun-Aesthetics: Released under the Creative Commons Attribution Share-Alike 4.0 License
SparkFun-Aesthetics: https://creativecommons.org/licenses/by-sa/4.0
